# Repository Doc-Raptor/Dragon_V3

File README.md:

Dragon V3 modular 3d/CNC controller series files

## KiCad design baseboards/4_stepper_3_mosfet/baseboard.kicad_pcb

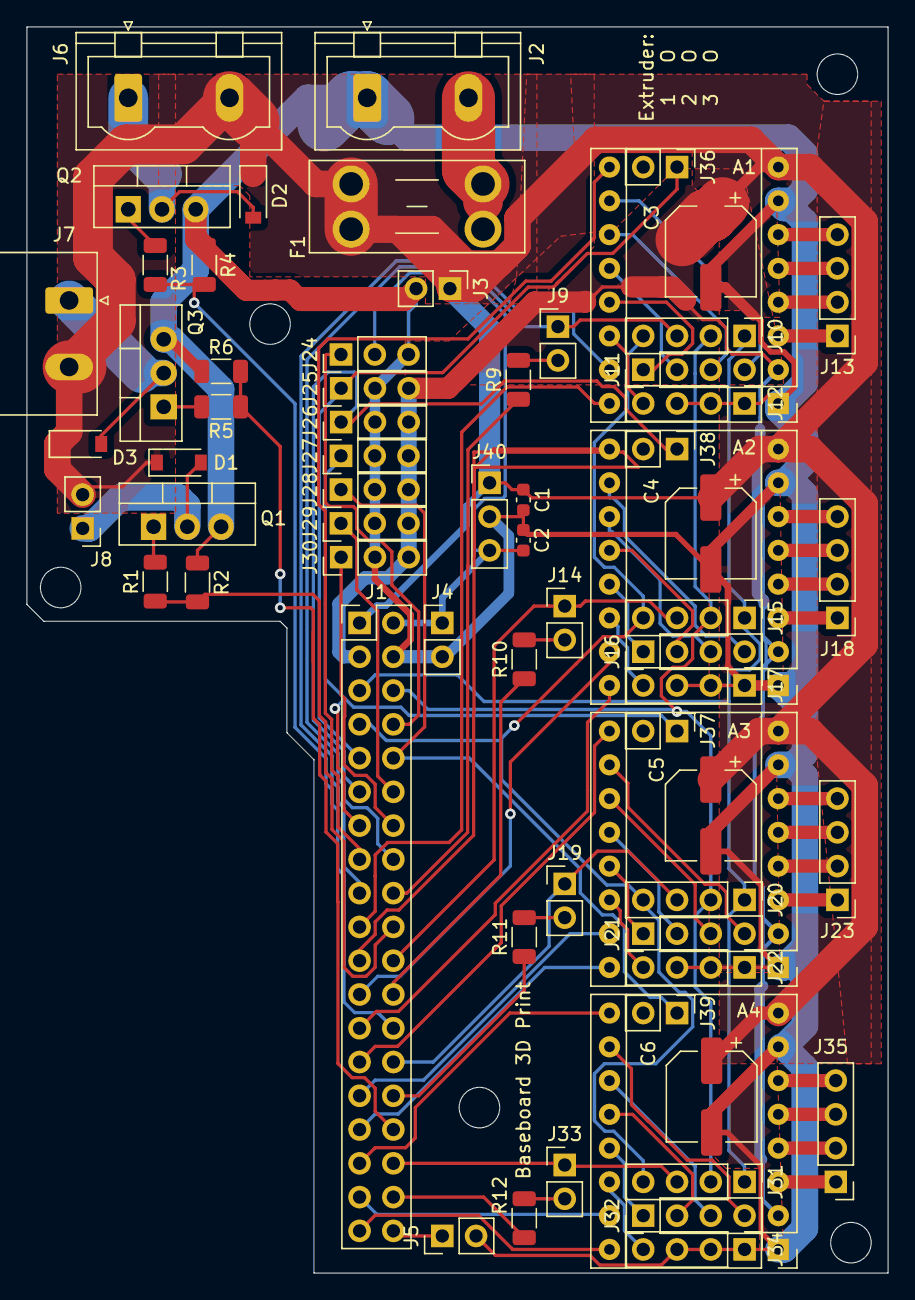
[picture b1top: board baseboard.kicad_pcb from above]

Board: 2 copper layers, 64.8 x 93.7 mm, 67 parts (0 on the bottom side), 85 nets.

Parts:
A1, A2, A3, A4: Pololu_Breakout_A4988; Pololu_Breakout-16_15.2x20.3mm
C1, C2: 10nF; C_0603_1608Metric
C3, C4, C5, C6: 100uF; CP_Elec_6.3x7.7
D1, D2, D3: 1N5819; D_SOD-123
F1: Fuse; Fuseholder_Blade_Mini_Keystone_3568
J1: MCU_Interface_0; PinHeader_2x19_P2.54mm_Vertical
J2: POWER_IN; PhoenixContact_GMSTBVA_2,5_2-G-7,62_1x02_P7.62mm_Vertical
J3: POWER_OUT; PinHeader_1x02_P2.54mm_Vertical
J4: 5V; PinHeader_1x02_P2.54mm_Vertical
J5: FET4; PinHeader_1x02_P2.54mm_Vertical
J6: FET2; PhoenixContact_GMSTBVA_2,5_2-G-7,62_1x02_P7.62mm_Vertical
J7: FET3; PhoenixContact_MSTBA_2,5_2-G_1x02_P5.00mm_Horizontal
J8: FET1; PinHeader_1x02_P2.54mm_Vertical
J9: UART_X; PinHeader_1x02_P2.54mm_Vertical
J10: X_TMC; PinHeader_1x04_P2.54mm_Vertical
J11: X_PIN; PinHeader_1x04_P2.54mm_Vertical
J12: X_GND; PinHeader_1x04_P2.54mm_Vertical
J13: X_STEPPER; PinHeader_1x04_P2.54mm_Vertical
J14: UART_Y; PinHeader_1x02_P2.54mm_Vertical
J15: Y_TMC; PinHeader_1x04_P2.54mm_Vertical
J16: Y_PIN; PinHeader_1x04_P2.54mm_Vertical
J17: Y_GND; PinHeader_1x04_P2.54mm_Vertical
J18: Y_STEPPER; PinHeader_1x04_P2.54mm_Vertical
J19: UART_Z; PinHeader_1x02_P2.54mm_Vertical
J20: Z_TMC; PinHeader_1x04_P2.54mm_Vertical
J21: Z_PIN; PinHeader_1x04_P2.54mm_Vertical
J22: Z_GND; PinHeader_1x04_P2.54mm_Vertical
J23: Z_STEPPER; PinHeader_1x04_P2.54mm_Vertical
J24: SERVO; PinHeader_1x03_P2.54mm_Vertical
J25: X-MIN; PinHeader_1x03_P2.54mm_Vertical
J26: Y-MIN; PinHeader_1x03_P2.54mm_Vertical
J27: Z-MIN; PinHeader_1x03_P2.54mm_Vertical
J28, J30: X-MAX; PinHeader_1x03_P2.54mm_Vertical
J29: Y-MAX; PinHeader_1x03_P2.54mm_Vertical
J31: E0_TMC; PinHeader_1x04_P2.54mm_Vertical
J32: E0_PIN; PinHeader_1x04_P2.54mm_Vertical
J33: UART_E0; PinHeader_1x02_P2.54mm_Vertical
J34: E0_GND; PinHeader_1x04_P2.54mm_Vertical
J35: E0_STEPPER; PinHeader_1x04_P2.54mm_Vertical
J36: Diag_X; PinHeader_1x02_P2.54mm_Vertical
J37: Diag_Z; PinHeader_1x02_P2.54mm_Vertical
J38: Diag_Y; PinHeader_1x02_P2.54mm_Vertical
J39: Diag_E0; PinHeader_1x02_P2.54mm_Vertical
J40: 5V_Regulator; PinHeader_1x03_P2.54mm_Vertical
Q1, Q2, Q3: IRF3205; TO-220-3_Vertical
R1, R3, R5: 100; R_1206_3216Metric
R2, R4, R6: 4K7; R_1206_3216Metric
R9, R10, R11, R12: 1K; R_1206_3216Metric

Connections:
+5V: C2.1, J1.2, J4.1, J24.2, J40.3
CS_RX_E0: J1.34, J31.3, J33.1
CS_RX_X: J1.16, J9.1, J10.3
CS_RX_Y: J1.22, J14.1, J15.3
CS_RX_Z: J1.28, J19.1, J20.3
DIR_E0: A4.16, J1.37
DIR_X: A1.16, J1.19
DIR_Y: A2.16, J1.25
DIR_Z: A3.16, J1.31
EN_E0: A4.9, J1.33
EN_X: A1.9, J1.15
EN_Y: A2.9, J1.21
EN_Z: A3.9, J1.27
FET1: J1.20, R1.1, R2.2
FET2: J1.26, R3.1, R4.2
FET3: J1.32, R5.1, R6.2
FET4: J1.38, J5.1
GND: A1.1, A1.7, A2.1, A2.7, A3.1, A3.7, A4.1, A4.7, C1.2, C2.2, C3.2, C4.2, C5.2, C6.2, J1.4, J2.1, J3.2, J4.2, J5.2, J12.1, J12.2, J12.3, J17.1, J17.2, J17.3, J22.1, J22.2, J22.3, J24.3, J25.2, J26.2, J27.2, J28.2, J29.2, J30.2, J34.1, J34.2, J34.3, J40.2, Q1.3, Q2.3, Q3.3, R2.1, R4.1, R6.1
Logic_PWR: A1.2, A2.2, A3.2, A4.2, J1.3, J25.3, J26.3, J27.3, J28.3, J29.3, J30.3
MISO: J1.7, J10.4, J15.4, J20.4, J31.4
MOSI: J1.5, J10.1, J15.1, J20.1, J31.1
unnamed: A1.3, J13.1
unnamed: A1.4, J13.2
unnamed: A1.5, J13.3
unnamed: A1.6, J13.4
unnamed: A1.10, J11.4
unnamed: A1.11, J11.3
unnamed: A1.12, J11.2
unnamed: A1.13, J11.1
unnamed: A1.14, J12.4
unnamed: A2.3, J18.1
unnamed: A2.4, J18.2
unnamed: A2.5, J18.3
unnamed: A2.6, J18.4
unnamed: A2.10, J16.4
unnamed: A2.11, J16.3
unnamed: A2.12, J16.2
unnamed: A2.13, J16.1
unnamed: A2.14, J17.4
unnamed: A3.3, J23.1
unnamed: A3.4, J23.2
unnamed: A3.5, J23.3
unnamed: A3.6, J23.4
unnamed: A3.10, J21.4
unnamed: A3.11, J21.3
unnamed: A3.12, J21.2
unnamed: A3.13, J21.1
unnamed: A3.14, J22.4
unnamed: A4.3, J35.1
unnamed: A4.4, J35.2
unnamed: A4.5, J35.3
unnamed: A4.6, J35.4
unnamed: A4.10, J32.4
unnamed: A4.11, J32.3
unnamed: A4.12, J32.2
unnamed: A4.13, J32.1
unnamed: A4.14, J34.4
unnamed: D1.2, J8.1, Q1.2
unnamed: D2.2, J6.1, Q2.2
unnamed: D3.2, J7.1, Q3.2
unnamed: F1.2, J2.2
unnamed: J9.2, R9.2
unnamed: J14.2, R10.2
unnamed: J19.2, R11.2
unnamed: J33.2, R12.2
unnamed: Q1.1, R1.2
unnamed: Q2.1, R3.2
unnamed: Q3.1, R5.2
SCK: J1.6, J10.2, J15.2, J20.2, J31.2
STEP_E0: A4.15, J1.35
STEP_X: A1.15, J1.17
STEP_Y: A2.15, J1.23
STEP_Z: A3.15, J1.29
SV0: J1.8, J24.1
TX_E0: J1.36, R12.1
TX_X: J1.18, R9.1
TX_Y: J1.24, R10.1
TX_Z: J1.30, R11.1
VDD: A1.8, A2.8, A3.8, A4.8, C1.1, C3.1, C4.1, C5.1, C6.1, D1.1, D2.1, D3.1, F1.1, J1.1, J3.1, J6.2, J7.2, J8.2, J40.1
X-MAX: J1.10, J28.1, J39.1
X-MIN: J1.9, J25.1, J36.1
Y-MAX: J1.12, J29.1
Y-MIN: J1.11, J26.1, J38.1
Z-MAX: J1.14, J30.1
Z-MIN: J1.13, J27.1, J37.1

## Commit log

2021-11-11 Added License
2021-11-11 readme update
2021-11-11 added 4S 3M baseboard
